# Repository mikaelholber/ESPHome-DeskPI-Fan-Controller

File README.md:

# ESPHome-Fan-Controller
The ESPHome-Fan-Controller was built gor a very specific purpose. To limit the noise while keeping the DeskPi rack cooled to a set temperature. 

My minilab is located in the bedroom and tucked away in such a way that I need good airflow at the lowest possible noise. To achive this i decided to use ESPHome to control a few 5V fans which can be mounted in the vented blanks available.

The schematics and ESPHome configuration is derived from https://github.com/patrickcollins12/esphome-fan-controller and the only original work is the PCB layout to fit the specific envelope in the vented blank. 

### This repository contains
* The KiCad schematics
* The KiCad PCB layout
* The KiCad Project file
* BOM and CPL for production at JLCPCB
* The ESPHome yaml files for manual control via either ESPHome webserver interface or Home Assistant
* The automation for Home Assistant to change fan speed based on Server CPU temp using Glances integration

### Board features
* The controller is based on the ESP32-S3-MINI-1-N4R2
* The controller fits neatly in a 40mm fan slot (32x32mm M3 screw holes) and features a vertical USB-C connector for programming and power. 

# Prepare the yaml
Change the friendly name to your liking and set the wifi-ssid and password.

# Programming
1. Install ESPHome and build (Install) the yaml file.
2. Choose plug into computer option.
3. Plug the controller into your computer and hold down the boot button WHILE selecting the Jtag in the pop-up window.
4. Wait for the firmware to install

If ESPhome returns an error before installing the firmware, try to hold the boot button WHILE plugging it into the computer. I'm not sure what order is required - Maybe see the documentation.

Check that the installation works by going to the name you choose .local

# Home Assistant
Install the ESPHome integration in Home Assistant.
Add a device and point to the local address of the Fan controller OR the IP-address.

I have 4 automations controlling the fans:
1. Setting the base speed at 7am to 60% (it gets warmer in the day)
2. Setting the base speed at 7.30pm to 30% (lower the noise in the night)
3. Set HIGH speed if the temperature goes above a certain temperature (See High-speed.yaml)
4. Set LOW speed if the temperature goes down again (See Low-speed.yaml)

# Purchasing boards
You can order boards in EU from me on Tindie: https://www.tindie.com/products/holber/minilab-esp-home-fan-controller-40x40mm

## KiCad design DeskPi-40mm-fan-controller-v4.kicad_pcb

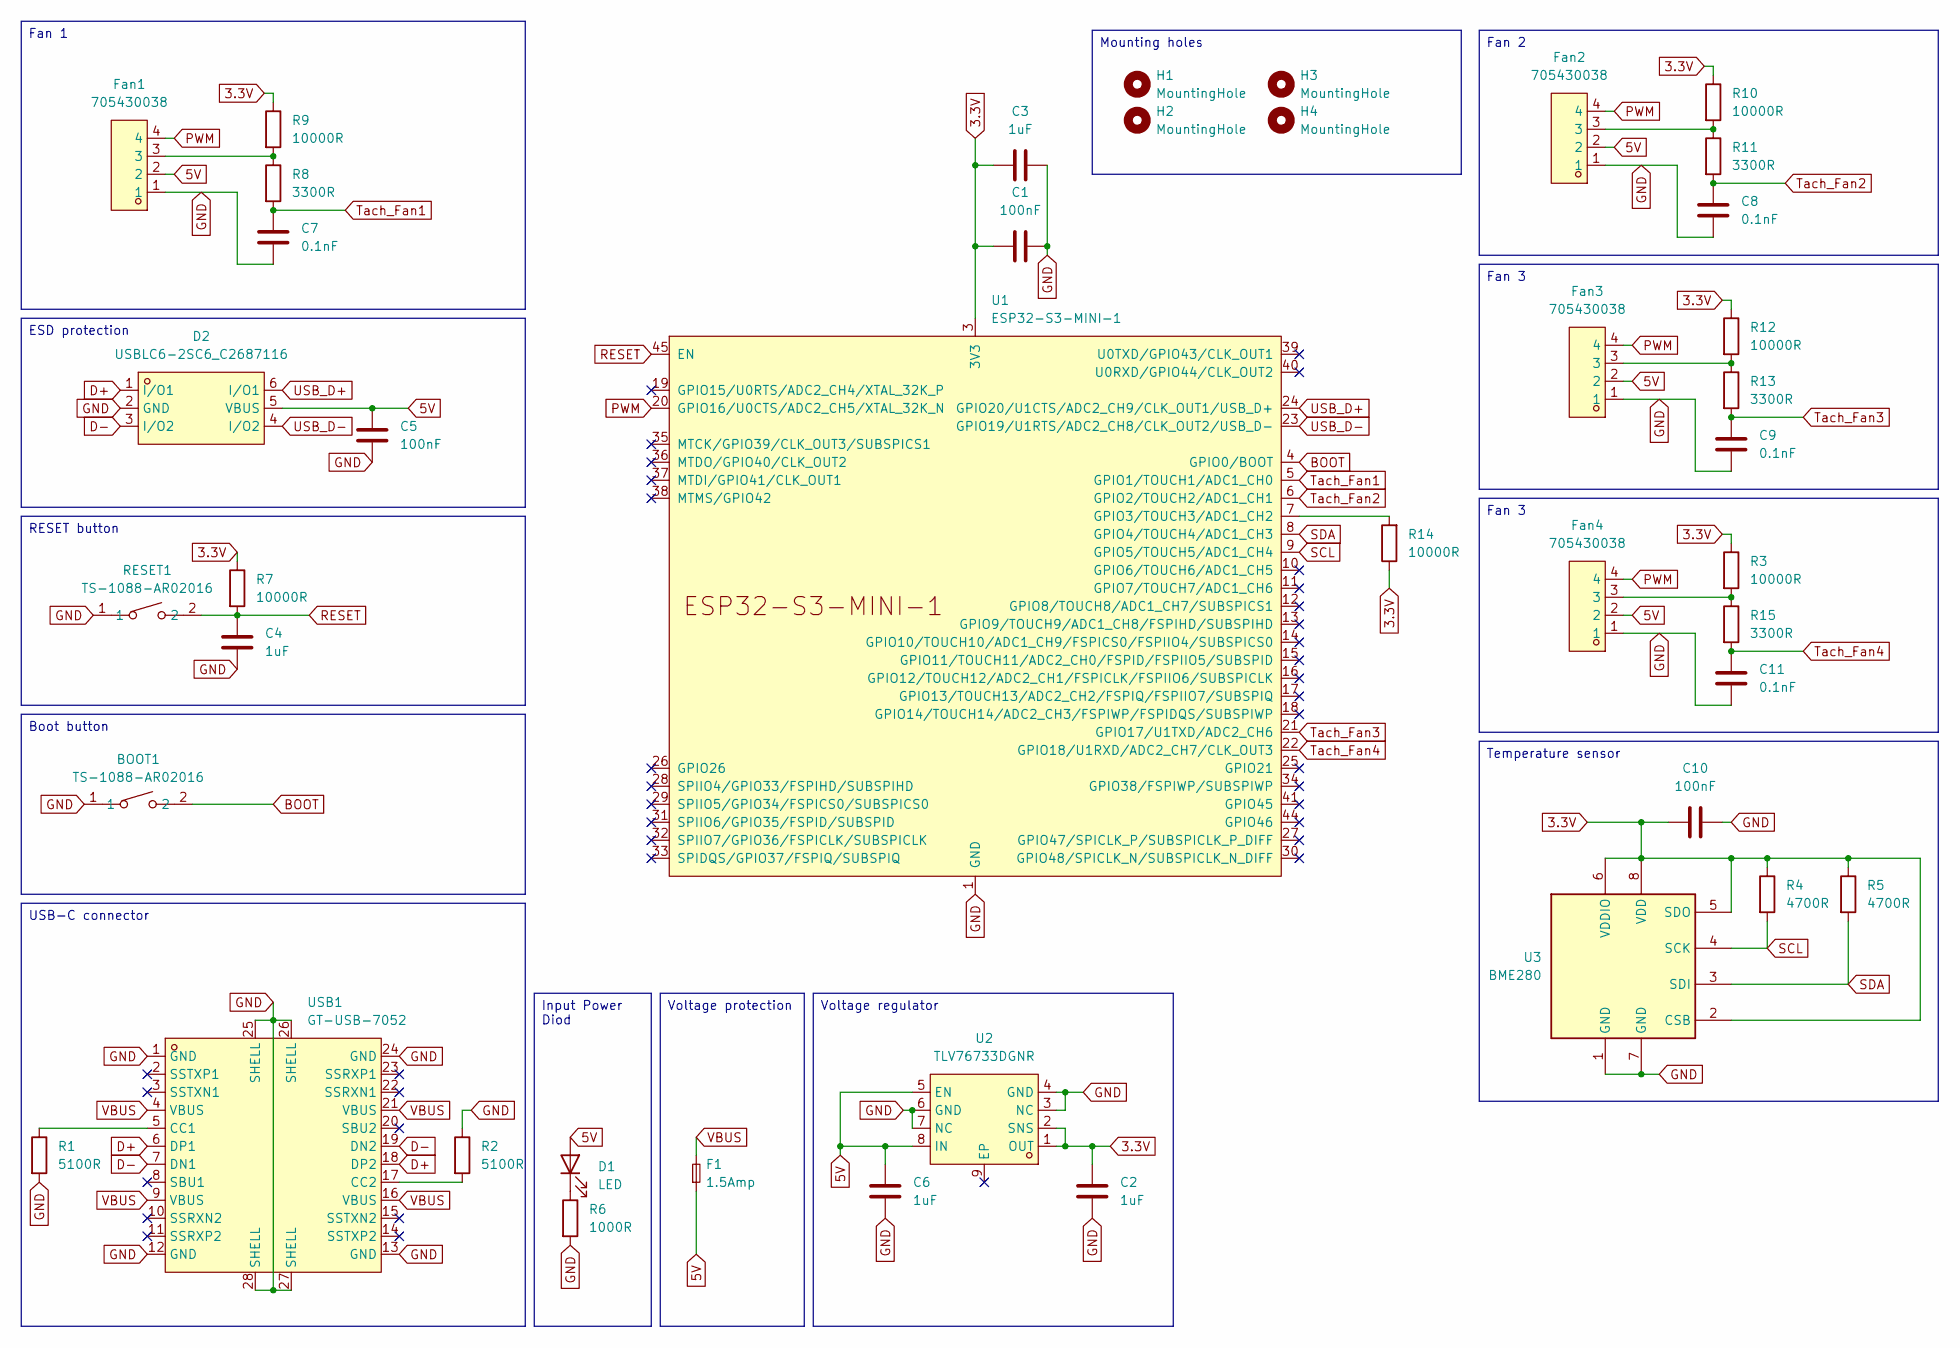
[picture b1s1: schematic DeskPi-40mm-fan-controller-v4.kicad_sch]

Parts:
BOOT1: TS-1088-AR02016; SW-SMD_L3.9-W3.0-P4.45; LCSC Part C720477
C1, C5, C10: 100nF; C_0402_1005Metric
C2, C3, C4, C6: 1uF; C_0402_1005Metric
C7, C8, C9, C11: 0.1nF; C_0402_1005Metric
D1: LED; LED_0603_1608Metric
D2: USBLC6-2SC6_C2687116; SOT-23-6_L2.9-W1.6-P0.95-LS2.8-BL; LCSC Part C2687116
F1: 1.5Amp; Fuse_0603_1608Metric
Fan1, Fan2, Fan3, Fan4: 705430038; CONN-TH_47053-1000; LCSC Part C240840
H1, H2, H3, H4: MountingHole; MountingHole_3.2mm_M3_DIN965_Pad
R1, R2: 5100R; R_0402_1005Metric
R3, R7, R9, R10, R12, R14: 10000R; R_0402_1005Metric
R4, R5: 4700R; R_0402_1005Metric
R6: 1000R; R_0402_1005Metric
R8, R11, R13, R15: 3300R; R_0402_1005Metric
RESET1: TS-1088-AR02016; SW-SMD_L3.9-W3.0-P4.45; LCSC Part C720477
U1: ESP32-S3-MINI-1
U2: TLV76733DGNR; MSOP-8_L3.0-W3.0-P0.65-LS4.9-BL-EP-1; LCSC Part C2873382
U3: BME280; Bosch_LGA-8_2.5x2.5mm_P0.65mm_ClockwisePinNumbering
USB1: GT-USB-7052; USB-C-SMD_GT-USB-7052_1; LCSC Part C963223

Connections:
3.3V: C1.1, C2.2, C3.2, C10.2, R3.1, R4.1, R5.1, R7.1, R9.1, R10.1, R12.1, R14.1, U1.3 (3V3), U2.1 (OUT), U2.2 (SNS), U3.2 (CSB), U3.5 (SDO), U3.6 (VDDIO), U3.8 (VDD)
5V: C5.2, C6.1, D1.2 (A), D2.5 (VBUS), F1.1, Fan1.2, Fan2.2, Fan3.2, Fan4.2, U2.5 (EN), U2.8 (IN)
BOOT: BOOT1.2, U1.4 (GPIO0/BOOT)
D+: D2.1 (I/O1), USB1.6 (DP1), USB1.18 (DP2)
D-: D2.3 (I/O2), USB1.7 (DN1), USB1.19 (DN2)
GND: BOOT1.1, C1.2, C2.1, C3.1, C4.1, C5.1, C6.2, C7.1, C8.1, C9.1, C10.1, C11.1, D2.2 (GND), Fan1.1, Fan2.1, Fan3.1, Fan4.1, R1.2, R2.1, R6.2, RESET1.1, U1.1 (GND), U1.2 (GND), U1.42 (GND), U1.43 (GND), U1.46 (GND), U1.47 (GND), U1.48 (GND), U1.49 (GND), U1.50 (GND), U1.51 (GND), U1.52 (GND), U1.53 (GND), U1.54 (GND), U1.55 (GND), U1.56 (GND), U1.57 (GND), U1.58 (GND), U1.59 (GND), U1.60 (GND), U1.61 (GND), U1.62 (GND), U1.63 (GND), U1.64 (GND), U1.65 (GND), U2.3 (NC), U2.4 (GND), U2.6 (GND), U2.7 (NC), U3.1 (GND), U3.7 (GND), USB1.1 (GND), USB1.12 (GND), USB1.13 (GND), USB1.24 (GND), USB1.25 (SHELL), USB1.26 (SHELL), USB1.27 (SHELL), USB1.28 (SHELL)
unnamed: D1.1 (K), R6.1
unnamed: Fan1.3, R8.1, R9.2
unnamed: Fan2.3, R10.2, R11.1
unnamed: Fan3.3, R12.2, R13.1
unnamed: Fan4.3, R3.2, R15.1
unnamed: R14.2, U1.7 (GPIO3/TOUCH3/ADC1_CH2)
unnamed: R1.1, USB1.5 (CC1)
unnamed: R2.2, USB1.17 (CC2)
PWM: Fan1.4, Fan2.4, Fan3.4, Fan4.4, U1.20 (GPIO16/U0CTS/ADC2_CH5/XTAL_32K_N)
RESET: C4.2, R7.2, RESET1.2, U1.45 (EN)
SCL: R4.2, U1.9 (GPIO5/TOUCH5/ADC1_CH4), U3.4 (SCK)
SDA: R5.2, U1.8 (GPIO4/TOUCH4/ADC1_CH3), U3.3 (SDI)
Tach_Fan1: C7.2, R8.2, U1.5 (GPIO1/TOUCH1/ADC1_CH0)
Tach_Fan2: C8.2, R11.2, U1.6 (GPIO2/TOUCH2/ADC1_CH1)
Tach_Fan3: C9.2, R13.2, U1.21 (GPIO17/U1TXD/ADC2_CH6)
Tach_Fan4: C11.2, R15.2, U1.22 (GPIO18/U1RXD/ADC2_CH7/CLK_OUT3)
USB_D+: D2.6 (I/O1), U1.24 (GPIO20/U1CTS/ADC2_CH9/CLK_OUT1/USB_D+)
USB_D-: D2.4 (I/O2), U1.23 (GPIO19/U1RTS/ADC2_CH8/CLK_OUT2/USB_D-)
VBUS: F1.2, USB1.4 (VBUS), USB1.9 (VBUS), USB1.16 (VBUS), USB1.21 (VBUS)

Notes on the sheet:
Fan 3
RESET button
Input Power Diod
ESD protection
Fan 2
Temperature sensor
Boot button
Voltage protection
USB-C connector
Fan 1
Mounting holes
Voltage regulator

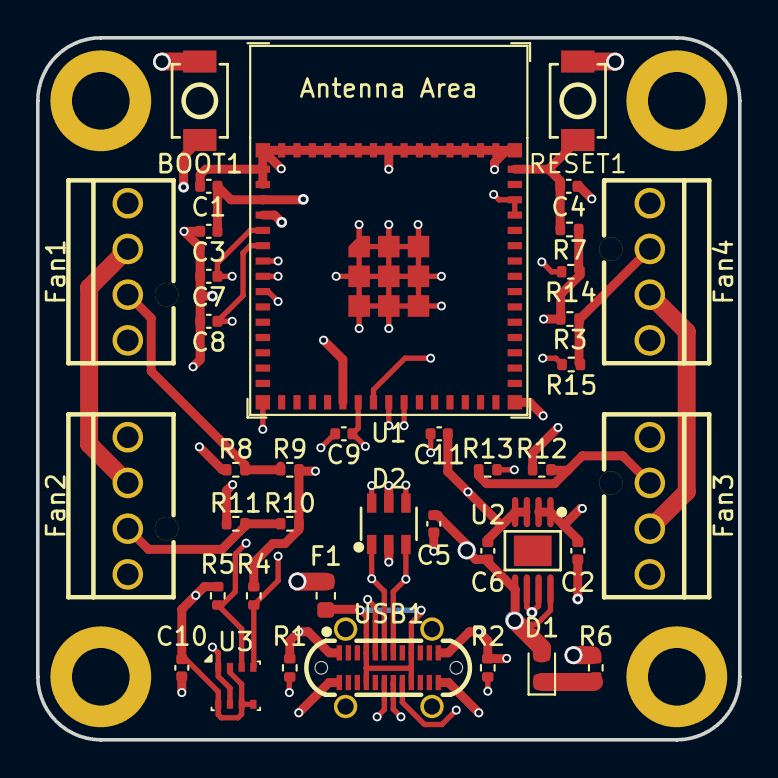
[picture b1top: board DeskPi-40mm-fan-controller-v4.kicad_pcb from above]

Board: 4 copper layers, 39.0 x 39.0 mm, 43 parts (0 on the bottom side), 25 nets.

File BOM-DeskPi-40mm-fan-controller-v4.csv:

Comment,Designator,Footprint,LCSC,Quantity
0.1nF,"C11,C7,C8,C9",C_0402_1005Metric,C1546,4
1.5Amp,F1,Fuse_0603_1608Metric,C126814,1
10000R,"R10,R12,R14,R3,R7,R9",R_0402_1005Metric,C25744,6
1000R,R6,R_0402_1005Metric,C11702,1
100nF,"C1,C10,C5",C_0402_1005Metric,C1525,3
1uF,"C2,C3,C4,C6",C_0402_1005Metric,C52923,4
3300R,"R11,R13,R15,R8",R_0402_1005Metric,C25890,4
4700R,"R4,R5",R_0402_1005Metric,C25900,2
5100R,"R1,R2",R_0402_1005Metric,C25905,2
705430038,"Fan1,Fan2,Fan3,Fan4",CONN-TH_47053-1000,C240840,4
BME280,U3,Bosch_LGA-8_2.5x2.5mm_P0.65mm_ClockwisePinNumbering,C92489,1
ESP32-S3-MINI-1,U1,ESP32-S3-MINI-1,C3013941,1
GT-USB-7052,USB1,USB-C-SMD_GT-USB-7052_1,C963223,1
LED,D1,LED_0603_1608Metric,C2286,1
TLV76733DGNR,U2,MSOP-8_L3.0-W3.0-P0.65-LS4.9-BL-EP-1,C2873382,1
TS-1088-AR02016,"BOOT1,RESET1",SW-SMD_L3.9-W3.0-P4.45,C720477,2
USBLC6-2SC6_C2687116,D2,SOT-23-6_L2.9-W1.6-P0.95-LS2.8-BL,C2687116,1

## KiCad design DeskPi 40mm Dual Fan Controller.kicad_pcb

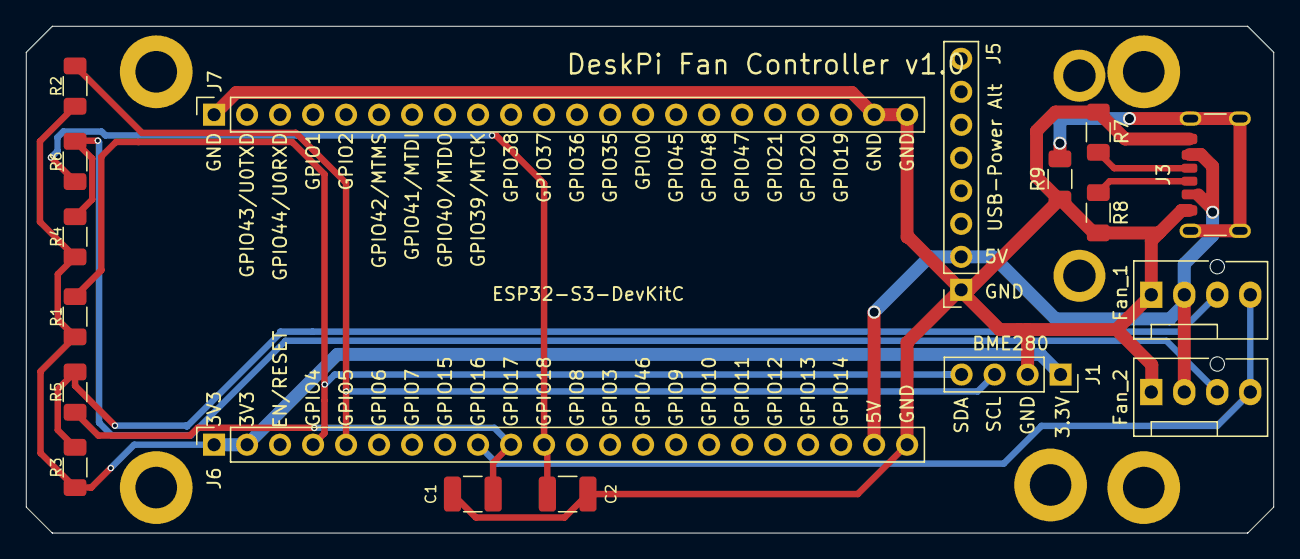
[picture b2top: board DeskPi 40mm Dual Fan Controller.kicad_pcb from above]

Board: 2 copper layers, 96.0 x 39.0 mm, 24 parts (0 on the bottom side), 13 nets.

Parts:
C1, C2: 0.1nF; C_1210_3225Metric_Pad1.33x2.70mm_HandSolder
H1, H4, H5, H8, H9: MountingHole; MountingHole_3.2mm_M3_DIN965_Pad
J1: BME280; PinSocket_1x04_P2.54mm_Vertical
J2: Fan_1; FanPinHeader_1x04_P2.54mm_Vertical
J3: USB_C_Receptacle_PowerOnly_6P; USB_C_Receptacle_GCT_USB4125-xx-x_6P_TopMnt_Horizontal
J4: Fan_2; FanPinHeader_1x04_P2.54mm_Vertical
J5: USB-C input; PinSocket_1x08_P2.54mm_Vertical
J6, J7: Conn_01x22_Socket; PinSocket_1x22_P2.54mm_Vertical
R1, R2, R5, R6: 3300R; R_1206_3216Metric_Pad1.30x1.75mm_HandSolder
R3, R4: 10000R; R_1206_3216Metric_Pad1.30x1.75mm_HandSolder
R7, R8: 5100R; R_1206_3216Metric_Pad1.30x1.75mm_HandSolder
R9: 1MR; R_1206_3216Metric_Pad1.30x1.75mm_HandSolder
U1: ESP32-S3-DevKitC

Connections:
3.3V: J1.1 (VIN), J6.1, J6.2, R1.1, R2.1, R3.1, R4.1
5V: J2.2 (5V), J3.A9 (VBUS), J3.B9 (VBUS), J4.2 (5V), J5.2 (VBUS), J6.21
GND: C1.1, C2.1, J1.2 (GND), J2.1 (GND), J3.A12 (GND), J3.B12 (GND), J4.1 (GND), J5.1 (GND), J6.22, J7.1, J7.21, J7.22, R7.2, R8.2, R9.1
unnamed: J3.A5 (CC1), R8.1
unnamed: J3.B5 (CC2), R7.1
unnamed: J3.S1 (SHIELD), R9.2
PWM: J2.4 (PWM), J4.4 (PWM), J6.9
SCL: J1.3 (SCL), J6.5, R2.2
SDA: J1.4 (SDA), J6.4, R1.2
Tach_Fan1: C1.2, J6.10, R5.1
Tach_Fan1_pullup: J2.3 (Tach), R3.2, R5.2
Tach_Fan2: C2.2, J6.11, R6.1
Tach_Fan2_pullup: J4.3 (Tach), R4.2, R6.2

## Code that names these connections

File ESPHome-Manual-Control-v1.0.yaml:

substitutions:
  friendly_name: Homelab Fan

esphome:
  name: homelab
  comment: ESP32 Temperature and Fan Controller

# Throttle writing parameters to the internal flash memory to reduce ESP memory wear / degradation
preferences:
  flash_write_interval: 15min

# Version of the board
esp32:
  variant: esp32s3

# Enable logging
logger:
  level: DEBUG

# Enable Home Assistant API
api:
  port: 6053
  batch_delay: 50ms  # Reduce latency for real-time applications
  listen_backlog: 2  # Allow 2 pending connections in queue
  max_connections: 6  # Allow up to 6 simultaneous connections
  max_send_queue: 10  # Maximum queued messages per connection before disconnect

ota:
  - platform: esphome
  
# WiFi connection to network
wifi:
  ssid: YOUR_SSID
  password: YOUR_CODE

  # Enable fallback hotspot (captive portal) in case wifi connection fails
  ap:
    ssid: "HomeLab-Fallback-Temp"
    password: "TESTPASS"

captive_portal:
text_sensor:

  # Send IP Address
  - platform: wifi_info
    ip_address:
      name: $friendly_name IP Address

  # Send Uptime in raw seconds
  - platform: template
    name: $friendly_name Uptime
    id: uptime_human
    icon: mdi:clock-start

# BME280 Temperature sensor specific configurations
i2c:
  sda: GPIO04
  scl: GPIO05
  scan: true
  id: bus_a

# BME280 Temperature sensor
sensor:
  - platform: bme280_i2c
    temperature:
      name: $friendly_name Temperature
      id: homelab_fan_temperature
      oversampling: 16x
    pressure:
      name: $friendly_name Pressure
    humidity:
      name: $friendly_name Humidity
    address: 0x77
    update_interval: 30s

####################
# Fan RPM counters #
####################
  - platform: pulse_counter
    pin: 
      number: GPIO1   # Connect to any input PIN on the ESP
      mode: INPUT_PULLUP
    unit_of_measurement: 'RPM'
    id: fan_1_speed
    name: Fan Speed 1
    accuracy_decimals: 0
    filters:
      - multiply: 0.5  # Depending on how many pulses the fan sends per round - should be 0.5 or 1 - try...

  - platform: pulse_counter
    pin: 
      number: GPIO2   # Connect to any input PIN on the ESP
      mode: INPUT_PULLUP
    unit_of_measurement: 'RPM'
    id: fan_2_speed
    name: Fan Speed 2
    accuracy_decimals: 0
    filters:
      - multiply: 0.5  # Depending on how many pulses the fan sends per round - should be 0.5 or 1 - try...

  - platform: pulse_counter
    pin: 
      number: GPIO17   # Connect to any input PIN on the ESP
      mode: INPUT_PULLUP
    unit_of_measurement: 'RPM'
    id: fan_3_speed
    name: Fan Speed 3
    accuracy_decimals: 0
    filters:
      - multiply: 0.5  # Depending on how many pulses the fan sends per round - should be 0.5 or 1 - try...

  - platform: template
    name: "Fan Speed (PWM Voltage)"
    unit_of_measurement: "%"
    id: fan_speed_pwm_voltage

###################################
# Report uptime to Home Assistant #
###################################
  - platform: uptime
    name: $friendly_name Uptime
    id: uptime_sensor
    update_interval: 60s
    on_raw_value:
      then:
        - text_sensor.template.publish:
            id: uptime_human
            # Custom C++ code to generate the result
            state: !lambda |-
              int seconds = round(id(uptime_sensor).raw_state);
              int days = seconds / (24 * 3600);
              seconds = seconds % (24 * 3600);
              int hours = seconds / 3600;
              seconds = seconds % 3600;
              int minutes = seconds /  60;
              seconds = seconds % 60;
              return (
                (days ? to_string(days) + "d " : "") +
                (hours ? to_string(hours) + "h " : "") +
                (minutes ? to_string(minutes) + "m " : "") +
                (to_string(seconds) + "s")
              ).c_str();

########################
# Fan speed controller #
########################
output:
  # Wire this pin (16) into the PWM pin of your 5v fan
  # ledc is the name of the pwm output system on an esp32
  - platform: ledc
    id: fan_speed
    pin: GPIO16

    # 25KHz is standard PC fan frequency, minimises buzzing
    frequency: "25000 Hz" 

    # my fans stop working below 13% powerful.
    # also they're  powerful and loud, cap their max speed to 80%
    min_power: 13%
    max_power: 80%

    # At 0, actually turn it off, otherwise the power keeps going.
    zero_means_zero: true

  - platform: template
    id: proxy_output
    type: float
    write_action:
      lambda: |-
        float write_val = 
          (id(manual_fan_control).state) ?
            id(manual_fan_control).speed / 100.0 : state*1.0;
        id(fan_speed).set_level(write_val);
        id(fan_speed_pwm_voltage).publish_state(write_val*100.0);

# If you turn this on, you can manually set the fan speed.
# The PID will be ignored. This is done via the proxy_output
fan:
  - platform: speed
    id: manual_fan_control
    output: proxy_output
    name: "Manual Fan Speed"
    restore_mode: ALWAYS_ON

switch:
  # Expose an ESP32 restart button to HA
  - platform: restart
    name: ${friendly_name} ESP32 Restart
    id: homelab_fan_restart

# Restart every day at 12:30am. 
# I've had some memory issues lockup 
# the device after a couple weeks
time:
  - platform: homeassistant
    on_time:
      # Every morning at 12:30am
    - seconds: 0
      minutes: 30
      hours: 0
      then:
       - switch.turn_on: homelab_fan_restart

# Webserver portal
web_server:
  port: 80

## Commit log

2025-12-11 KiCad files for v1.0
    KiCad 9.0 files for DeskPi 40mm Dual Fan Controller board v1.0
2025-12-28 Update README.md
    Update
2026-02-02 Update ESPHome-Manual-Control-v3.0yaml
    Written to support design 3.0
2026-02-03 Change to fully integrated chip
2026-02-03 Home assistant automations
